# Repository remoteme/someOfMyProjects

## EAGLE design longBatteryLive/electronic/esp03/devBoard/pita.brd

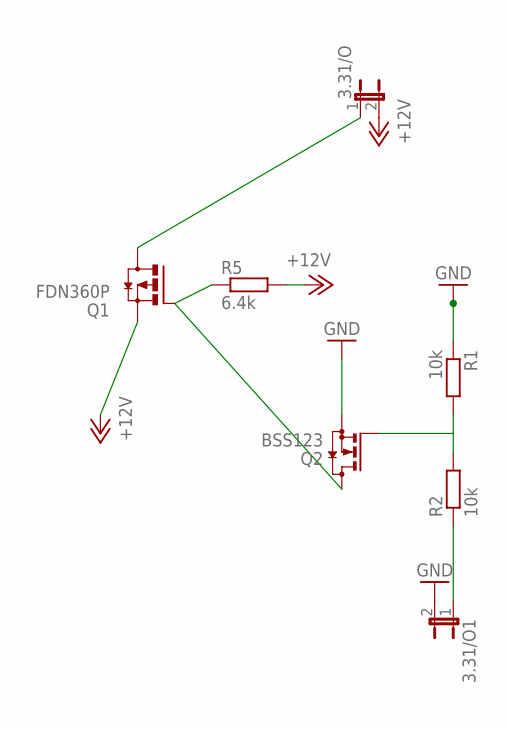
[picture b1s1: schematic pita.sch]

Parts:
3.31/O, 3.31/O1: JP1E; JP1
Q1: FDN360P; SUPER-SOT3
Q2: BSS123; SOT23
R1, R2: 10k; 0204/5
R5: 6.4k; 0204/7

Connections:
+12V: 3.31/O.2, Q1.2 (S), R5.2
ARD_TR: 3.31/O1.1, R2.1
GND: 3.31/O1.2, Q2.2 (S), R1.1
unnamed: Q2.1 (G), R1.2, R2.2
unnamed: 3.31/O.1, Q1.3 (D)
ON/OFF_GND: Q1.1 (G), Q2.3 (D), R5.1

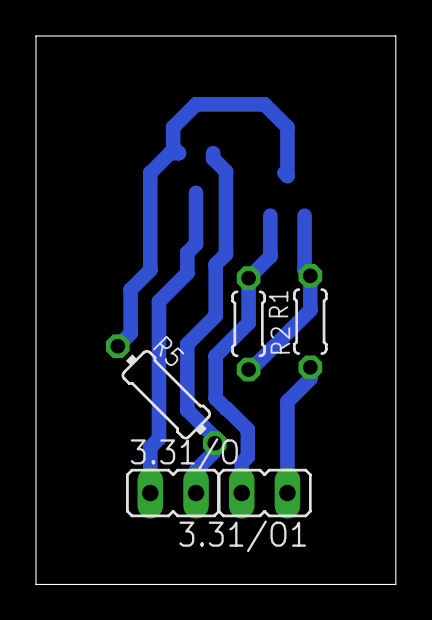
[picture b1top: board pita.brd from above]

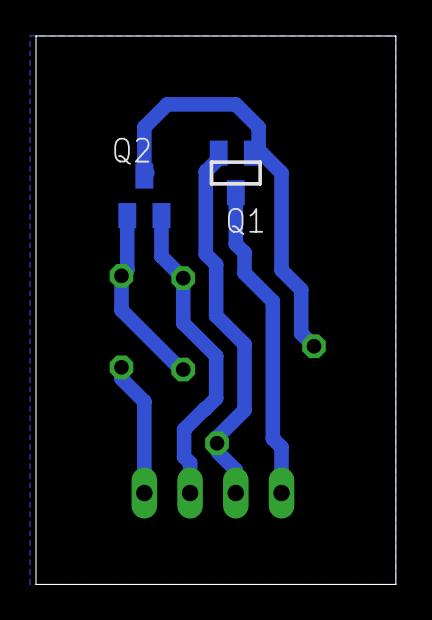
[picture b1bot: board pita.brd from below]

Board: 2 copper layers, 20.0 x 30.5 mm, 7 parts (2 on the bottom side), 6 nets.

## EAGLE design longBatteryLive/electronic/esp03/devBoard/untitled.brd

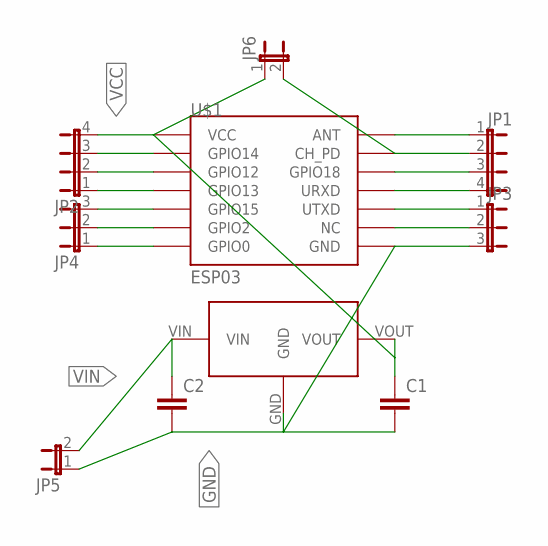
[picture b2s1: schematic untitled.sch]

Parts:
C1, C2: CC0603; C0603
JP1, JP2: JP4E; JP4
JP3, JP4: JP2E; JP2
JP5, JP6: JP1E; JP1
U$1: ESP03
U$3: HT7333; SOT89

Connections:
GND: C1.2, C2.2, JP3.3, JP5.1, U$1.GND, U$3.GND
unnamed: JP1.1, U$1.ANT
unnamed: JP1.2, JP6.2, U$1.CH_PD
unnamed: JP1.3, U$1.GPIO18
unnamed: JP1.4, U$1.URXD
unnamed: JP3.1, U$1.UTXD
unnamed: JP3.2, U$1.NC
unnamed: JP2.3, U$1.GPIO14
unnamed: JP2.2, U$1.GPIO12
unnamed: JP2.1, U$1.GPIO13
unnamed: JP4.3, U$1.GPIO15
unnamed: JP4.2, U$1.GPIO2
unnamed: JP4.1, U$1.GPIO0
VCC: C1.1, JP2.4, JP6.1, U$1.VCC, U$3.VOUT
VIN: C2.1, JP5.2, U$3.VIN

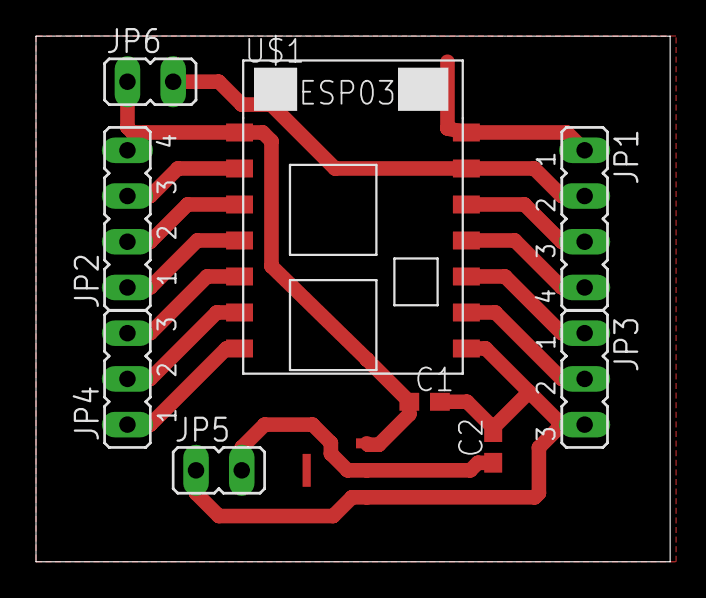
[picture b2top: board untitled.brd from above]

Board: 2 copper layers, 35.2 x 29.2 mm, 10 parts (0 on the bottom side), 15 nets.

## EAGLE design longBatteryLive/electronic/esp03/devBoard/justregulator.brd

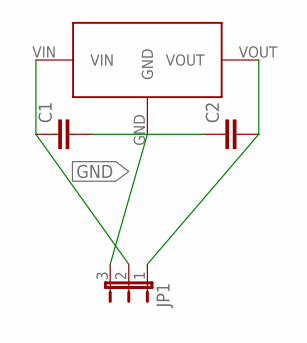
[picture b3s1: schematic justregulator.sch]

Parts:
C1, C2: C-EUC0603; C0603
JP1: JP2E; JP2
U$1: HT7333; SOT89

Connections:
GND: C1.2, C2.1, JP1.3, U$1.GND
unnamed: C1.1, JP1.2, U$1.VIN
unnamed: C2.2, JP1.1, U$1.VOUT

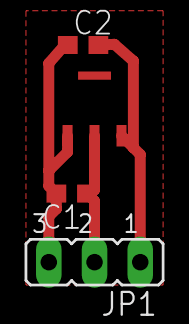
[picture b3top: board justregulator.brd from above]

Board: 2 copper layers, 4 parts (0 on the bottom side), 3 nets.

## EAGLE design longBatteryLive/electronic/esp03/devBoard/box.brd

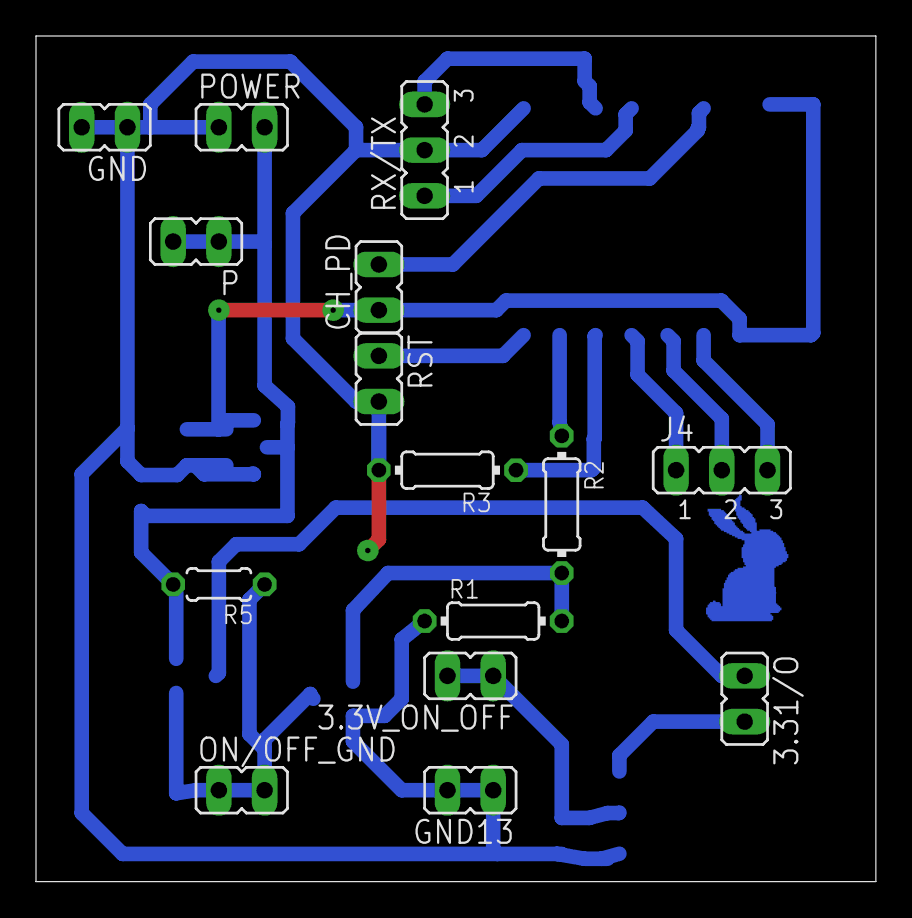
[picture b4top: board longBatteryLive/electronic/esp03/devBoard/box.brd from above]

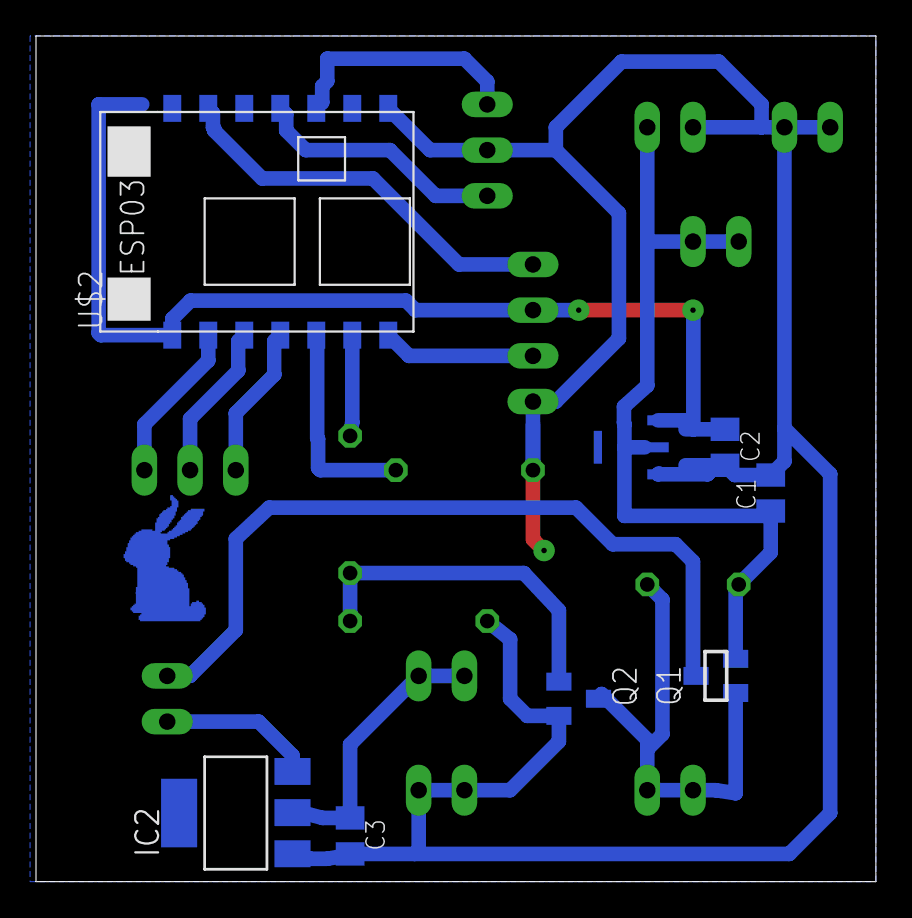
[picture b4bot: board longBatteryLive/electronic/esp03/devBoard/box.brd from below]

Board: 2 copper layers, 46.7 x 47.0 mm, 23 parts (8 on the bottom side), 17 nets.

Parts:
3.3V_ON_OFF, 3.31/O: JP1
C1, C2: 0.1; C0805K
C3: 22uF; C0805K
CH_PD: JP1
GND, GND13: GND; JP1
IC2: REG1117; SOT223
J4: JP2
ON/OFF_GND: JP1
P: 12V; JP1
POWER: 12V; JP1
Q1: FDN360P; SUPER-SOT3
Q2: BSS123; SOT23
R1, R2, R3: 10k; 0204/7
R5: 6.4k; 0204/5
RST: JP1
RX/TX: JP2
U$2: ESP03
U$3: HT7333; SOT89

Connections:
3.3I/OOUT: 3.3V_ON_OFF.1, 3.3V_ON_OFF.2, C3.1, IC2.2
+3.3V: C2.1, CH_PD.1, U$2.VCC, U$3.VOUT
+12V: C1.1, P.1, P.2, POWER.2, Q1.2, R5.2, U$3.VIN
ARD_TR: R2.1, U$2.GPIO2
CH_PD: CH_PD.2, U$2.CH_PD
GND: C1.2, C2.2, C3.2, GND.1, GND.2, GND13.1, GND13.2, IC2.1, POWER.1, Q2.2, R1.1, R3.2, RST.2, RX/TX.2, U$2.GND, U$3.GND
unnamed: Q2.1, R1.2, R2.2
unnamed: 3.31/O.1, Q1.3
unnamed: R3.1, U$2.GPIO15
unnamed: J4.1, U$2.GPIO13
unnamed: J4.2, U$2.GPIO12
unnamed: J4.3, U$2.GPIO14
unnamed: 3.31/O.2, IC2.3
unnamed: RST.1, U$2.GPIO0
ON/OFF_GND: ON/OFF_GND.1, ON/OFF_GND.2, Q1.1, Q2.3, R5.1
RX: RX/TX.1, U$2.URXD
TX: RX/TX.3, U$2.UTXD

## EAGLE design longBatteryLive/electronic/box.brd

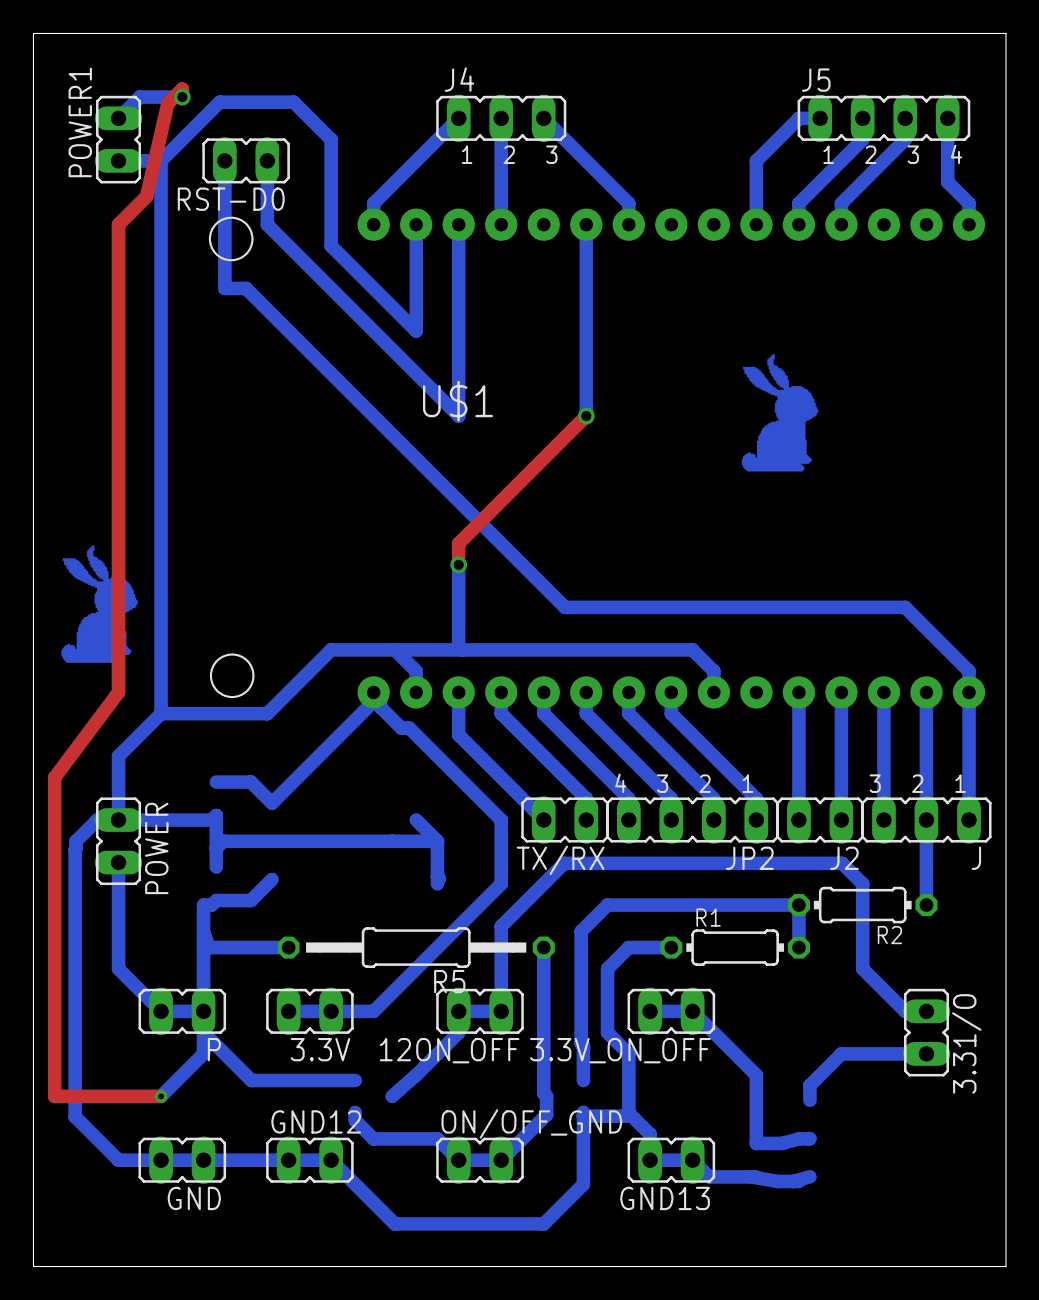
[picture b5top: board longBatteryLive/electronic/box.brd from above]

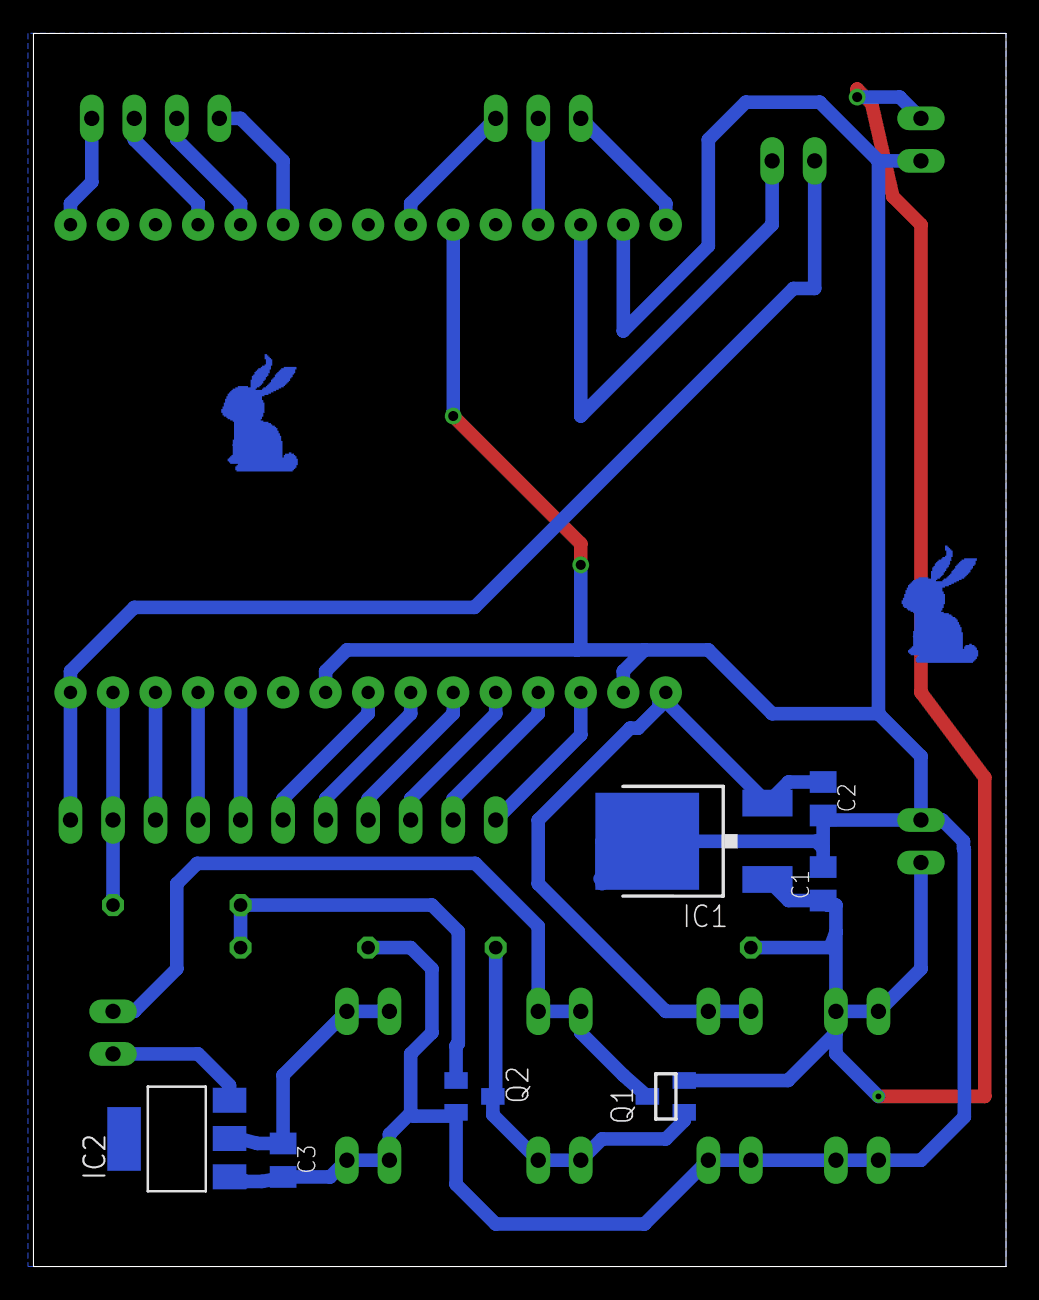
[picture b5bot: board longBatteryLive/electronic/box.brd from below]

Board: 2 copper layers, 58.1 x 73.7 mm, 29 parts (7 on the bottom side), 27 nets.

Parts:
3.3V, 3.3V_ON_OFF, 3.31/O, 12ON_OFF: JP1
C1, C2: 0.1; C0805K
C3: 22uF; C0805K
GND, GND12, GND13: GND; JP1
IC1: LP2950CDT-3.3; DPACK
IC2: REG1117; SOT223
J, J4: JP2
J2: JP1
J5: JP4
JP2: JP4
ON/OFF_GND: JP1
P: 12V; JP1
POWER, POWER1: 12V; JP1
Q1: FDN360P; SUPER-SOT3
Q2: BSS123; SOT23
R1, R2: 10k; 0204/7
R5: 6.4k; 0207/15
RST-D0: JP1
TX/RX: JP1
U$1: ESP12_DEVKIT

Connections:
+5V: 3.3V.1, 3.3V.2, C2.1, IC1.3, U$1.3V3@2
+12V: C1.1, IC1.1, P.1, P.2, POWER.2, POWER1.2, Q1.2, R5.2
ARD_TR: J.2, R2.1, U$1.D1
GND: C1.2, C2.2, C3.2, GND.1, GND.2, GND12.1, GND12.2, GND13.1, GND13.2, IC1.4, IC2.1, POWER.1, POWER1.1, Q2.2, R1.1, U$1.GND@0, U$1.GND@1, U$1.GND@2, U$1.GND@3
unnamed: 3.3V_ON_OFF.1, 3.3V_ON_OFF.2, C3.1, IC2.2
unnamed: Q2.1, R1.2, R2.2
unnamed: 3.31/O.1, 12ON_OFF.1, 12ON_OFF.2, Q1.3
unnamed: RST-D0.1, U$1.RST
unnamed: J.1, RST-D0.2, U$1.D0
unnamed: J5.4, U$1.A0
unnamed: J5.3, U$1.S3
unnamed: J5.2, U$1.S2
unnamed: J5.1, U$1.S1
unnamed: JP2.4, U$1.D8
unnamed: JP2.3, U$1.D7
unnamed: JP2.2, U$1.D6
unnamed: JP2.1, U$1.D5
unnamed: 3.31/O.2, IC2.3
unnamed: J.3, U$1.D2
unnamed: J2.1, U$1.D3
unnamed: J2.2, U$1.D4
unnamed: TX/RX.1, U$1.RX
unnamed: TX/RX.2, U$1.TX
unnamed: J4.3, U$1.SK
unnamed: J4.2, U$1.EN
unnamed: J4.1, U$1.VI
ON/OFF_GND: ON/OFF_GND.1, ON/OFF_GND.2, Q1.1, Q2.3, R5.1

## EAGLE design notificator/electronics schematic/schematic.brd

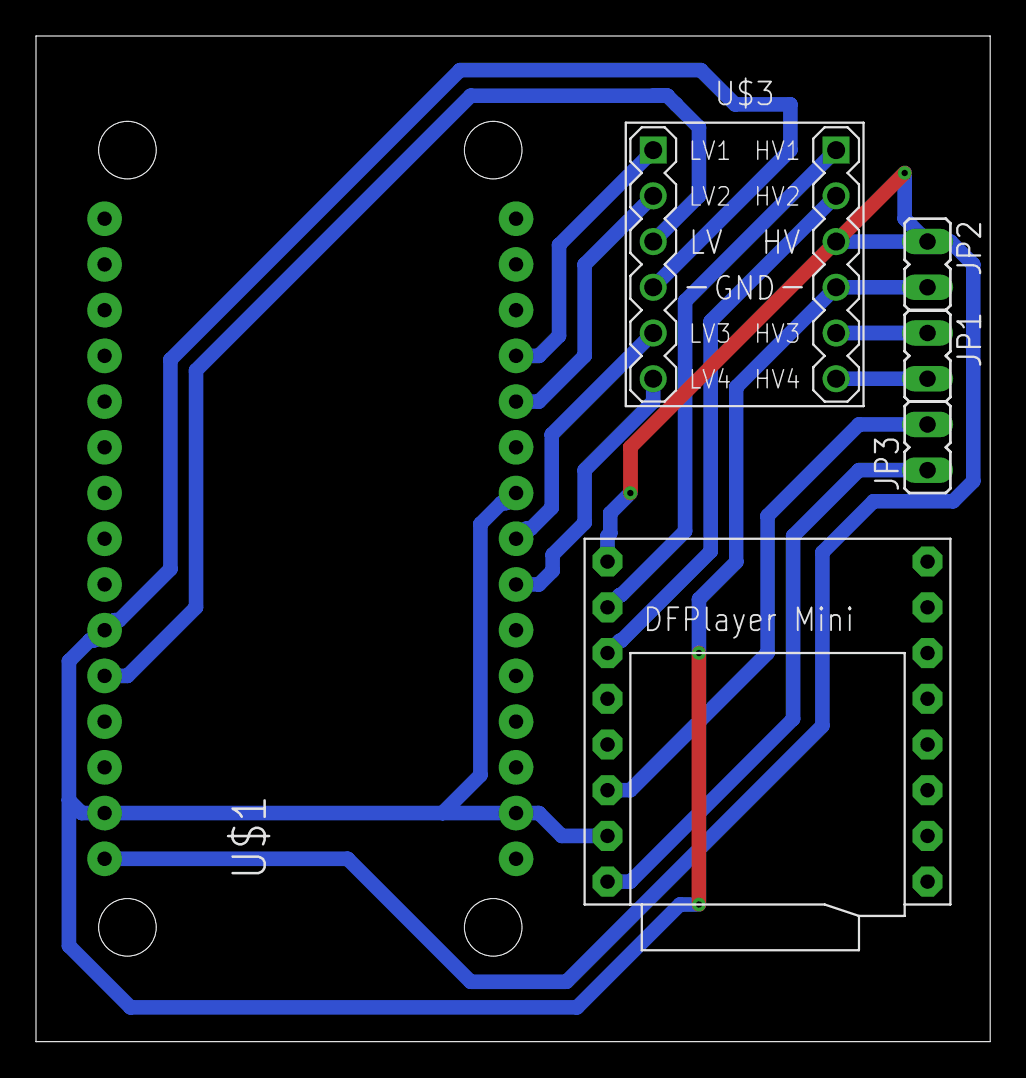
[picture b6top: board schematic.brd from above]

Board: 2 copper layers, 53.0 x 55.9 mm, 6 parts (0 on the bottom side), 13 nets.

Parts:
JP1, JP2, JP3: JP1
U$1: ESP12E_DEVKIT
U$2: DFPLAYER
U$3: LEVEL-SHIFTER-4CH

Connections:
3,3V: U$1.3V3@0, U$3.J1.3
GND: JP2.2, U$1.GND@0, U$1.GND@1, U$1.GND@2, U$1.GND@3, U$2.GND_1, U$3.J1.4, U$3.J2.4
unnamed: JP1.1, U$3.J2.5
unnamed: JP1.2, U$3.J2.6
unnamed: U$1.D3, U$3.J1.1
unnamed: U$1.D4, U$3.J1.2
unnamed: U$1.D5, U$3.J1.5
unnamed: U$1.D6, U$3.J1.6
unnamed: U$2.RX, U$3.J2.1
unnamed: U$2.TX, U$3.J2.2
unnamed: JP3.2, U$2.SPK1
unnamed: JP3.1, U$2.SPK2
VCC: JP2.1, U$1.VIN, U$2.VCC, U$3.J2.3

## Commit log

2018-02-17 add emergency light
2018-02-24 final version of cmaera with servi and light
2018-03-15 temp press humm
2018-03-18 text temperature humm and press
2018-03-18 next weatherstation
2018-03-22 add files
2018-03-22 add library
2018-03-24 update switcher
2018-03-27 diodeWithButton
2018-03-27 next tutorial and bugs
2018-03-28 cosmetics + graphics
2018-03-29 update for tutorial
2018-03-31 some small chagnes
2018-04-01 temperature on request
2018-04-02 add electronics for siren
2018-04-09 next
2018-05-03 better webpage
2018-05-07 next remoteme
2018-05-26 with ping
2018-05-31 libraries up
2018-05-31 added some missing files
2018-06-01 next for tutorial
2018-06-01 remove wifi auth
2018-06-03 temperature on graph
2018-06-03 temperature on graph for tutorial
2018-06-13 draging files
2018-06-17 add dump example
2018-06-24 ftpserver
2018-06-24 clear passwords
2018-06-25 car 2wd
2018-06-29 next with ftp creditentials
2018-06-30 next for car
2018-07-03 next websocket server inner
2018-07-04 updates libraries
2018-07-05 next car and better remoteme
2018-07-05 libraries update to won hosting
2018-07-05 better look at mobile phone
2018-07-08 aruino car update
2018-07-13 arduino remote lite
2018-07-15 better exception handlers and new files
2018-07-16 update diode with button
2018-07-16 add rasbperrypi click button
2018-07-17 file for python
2018-07-22 repair sending pythong messages
2018-08-02 next observers
2018-08-03 next observers and simple example
2018-08-06 added more types
2018-08-07 repair
2018-08-07 add observer echo
2018-08-09 add observer car
2018-08-18 add logout and analitics
2018-08-19 project structure reorganize
2018-08-20 reorganize
2018-08-24 next better obsevables
2018-09-02 next variables
2018-09-09 addCOmponent Starter
2018-09-09 add code
2018-09-12 add code generator for python
2018-10-14 slef histing libraries
2018-10-14 next variables change
2018-10-18 arduino car variables based
2018-10-18 rename packeges - error with direct connections
2018-11-14 updete remoteMe.js
2018-12-26 add more tutorials
2019-02-04 schamtics for PCB

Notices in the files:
parts and their libraries:
diy-modules: Released under the Creative Commons Attribution 4.0 International License: http://creativecommons.org/licenses/by/4.0
